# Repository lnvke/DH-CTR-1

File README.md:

DH/CTR-1. The successor to the DH/CTR-0. Now with more sensible design.

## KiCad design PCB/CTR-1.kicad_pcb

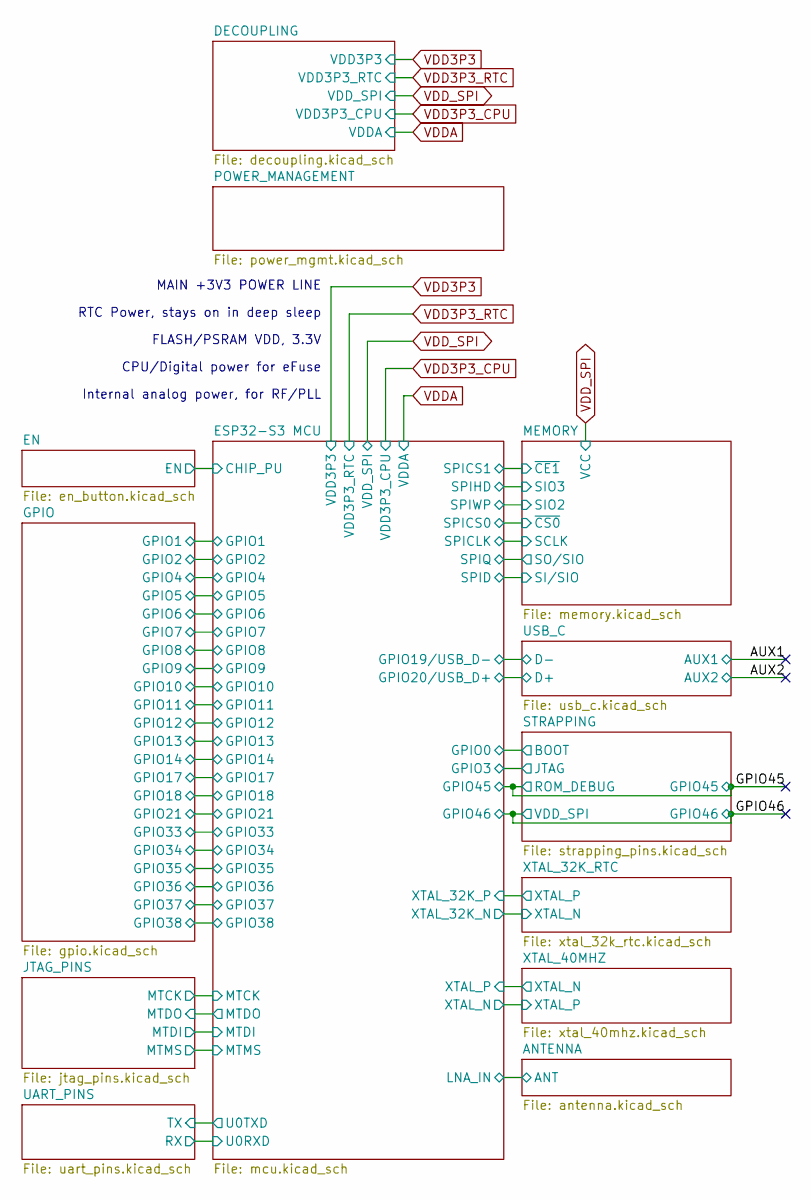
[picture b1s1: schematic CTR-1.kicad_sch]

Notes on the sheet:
Internal analog power, for RF/PLL
CPU/Digital power for eFuse
RTC Power, stays on in deep sleep
MAIN +3V3 POWER LINE
FLASH/PSRAM VDD, 3.3V

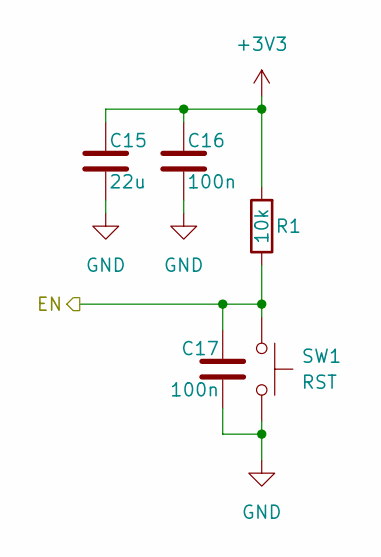
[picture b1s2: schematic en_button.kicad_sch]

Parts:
C15: 22u; C_0805_2012Metric
C16, C17: 100n; C_0603_1608Metric
R1: 10k; R_0603_1608Metric
SW1: RST; SW_Push_SPST_NO_Alps_SKRK

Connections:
+3V3: C15.1, C16.1, R1.2; also elsewhere on the board
/EN/EN: C17.1, R1.1, SW1.1; also elsewhere on the board
GND: C15.2, C16.2, C17.2, SW1.2; also elsewhere on the board

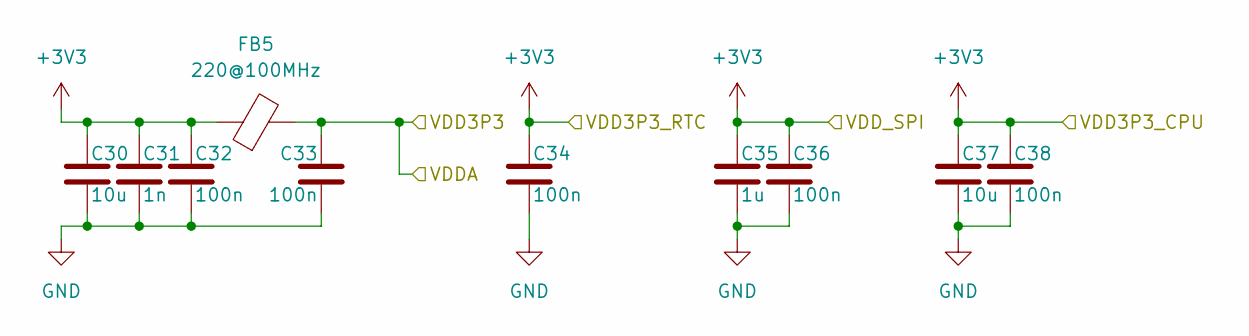
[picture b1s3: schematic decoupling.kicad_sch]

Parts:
C30: 10u; C_0805_2012Metric
C31: 1n; C_0402_1005Metric
C32: 100n; C_0402_1005Metric
C33, C34, C36, C38: 100n; C_0603_1608Metric
C35: 1u; C_0805_2012Metric
C37: 10u; C_0603_1608Metric
FB5: 220@100MHz; L_0805_2012Metric

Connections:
GND: C30.2, C31.2, C32.2, C33.2, C34.2, C35.2, C36.2, C37.2, C38.2; also elsewhere on the board
VDD3P3_RTC: C30.1, C31.1, C32.1, C34.1, C35.1, C36.1, C37.1, C38.1, FB5.1; also elsewhere on the board
VDDA: C33.1, FB5.2; also elsewhere on the board

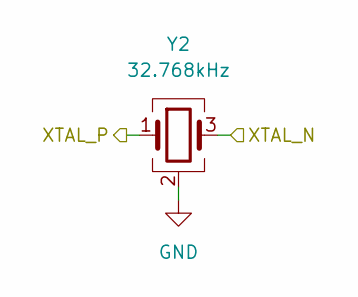
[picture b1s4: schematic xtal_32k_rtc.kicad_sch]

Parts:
Y2: 32.768kHz; Crystal_SMD_3225-4Pin_3.2x2.5mm

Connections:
/ESP32-S3 MCU/XTAL_32K_N: Y2.3; also elsewhere on the board
/ESP32-S3 MCU/XTAL_32K_P: Y2.1; also elsewhere on the board
GND: Y2.2 (G), Y2.4 (G); also elsewhere on the board

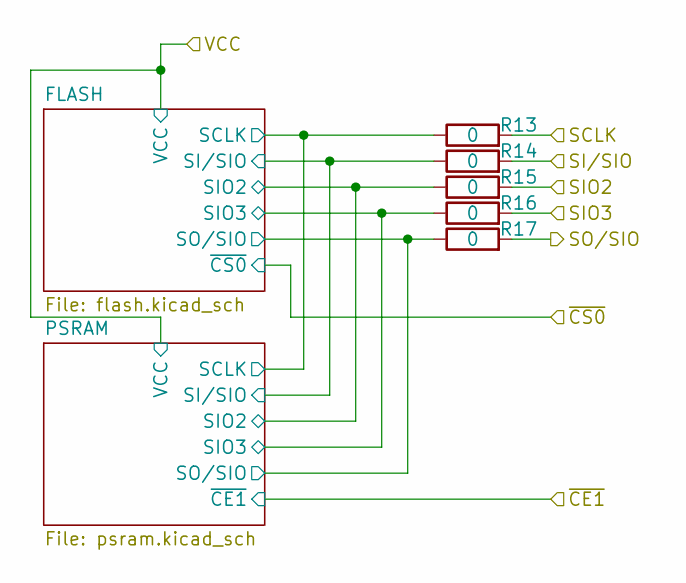
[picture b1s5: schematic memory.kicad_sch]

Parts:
R13, R14, R15, R16, R17: 0; R_0402_1005Metric

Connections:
/ESP32-S3 MCU/SPICLK: R13.2; also elsewhere on the board
/ESP32-S3 MCU/SPID: R14.2; also elsewhere on the board
/ESP32-S3 MCU/SPIHD: R16.2; also elsewhere on the board
/ESP32-S3 MCU/SPIQ: R17.2; also elsewhere on the board
/ESP32-S3 MCU/SPIWP: R15.2; also elsewhere on the board
/MEMORY/FLASH/SCLK: R13.1; also elsewhere on the board
/MEMORY/FLASH/SIO2: R15.1; also elsewhere on the board
/MEMORY/FLASH/SIO3: R16.1; also elsewhere on the board
/MEMORY/FLASH/SI/SIO: R14.1; also elsewhere on the board
/MEMORY/FLASH/SO/SIO: R17.1; also elsewhere on the board

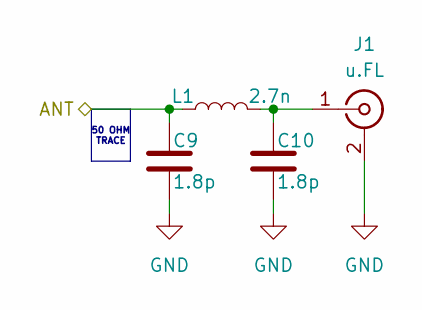
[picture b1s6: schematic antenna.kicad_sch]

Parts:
C9, C10: 1.8p; C_0603_1608Metric
J1: u.FL; U.FL_Hirose_U.FL-R-SMT-1_Vertical
L1: 2.7n; L_0402_1005Metric

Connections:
/ANTENNA/ANT: C9.1, L1.1; also elsewhere on the board
GND: C9.2, C10.2, J1.2 (Ext); also elsewhere on the board
unnamed: C10.1, J1.1 (In), L1.2

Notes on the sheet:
50 OHM TRACE

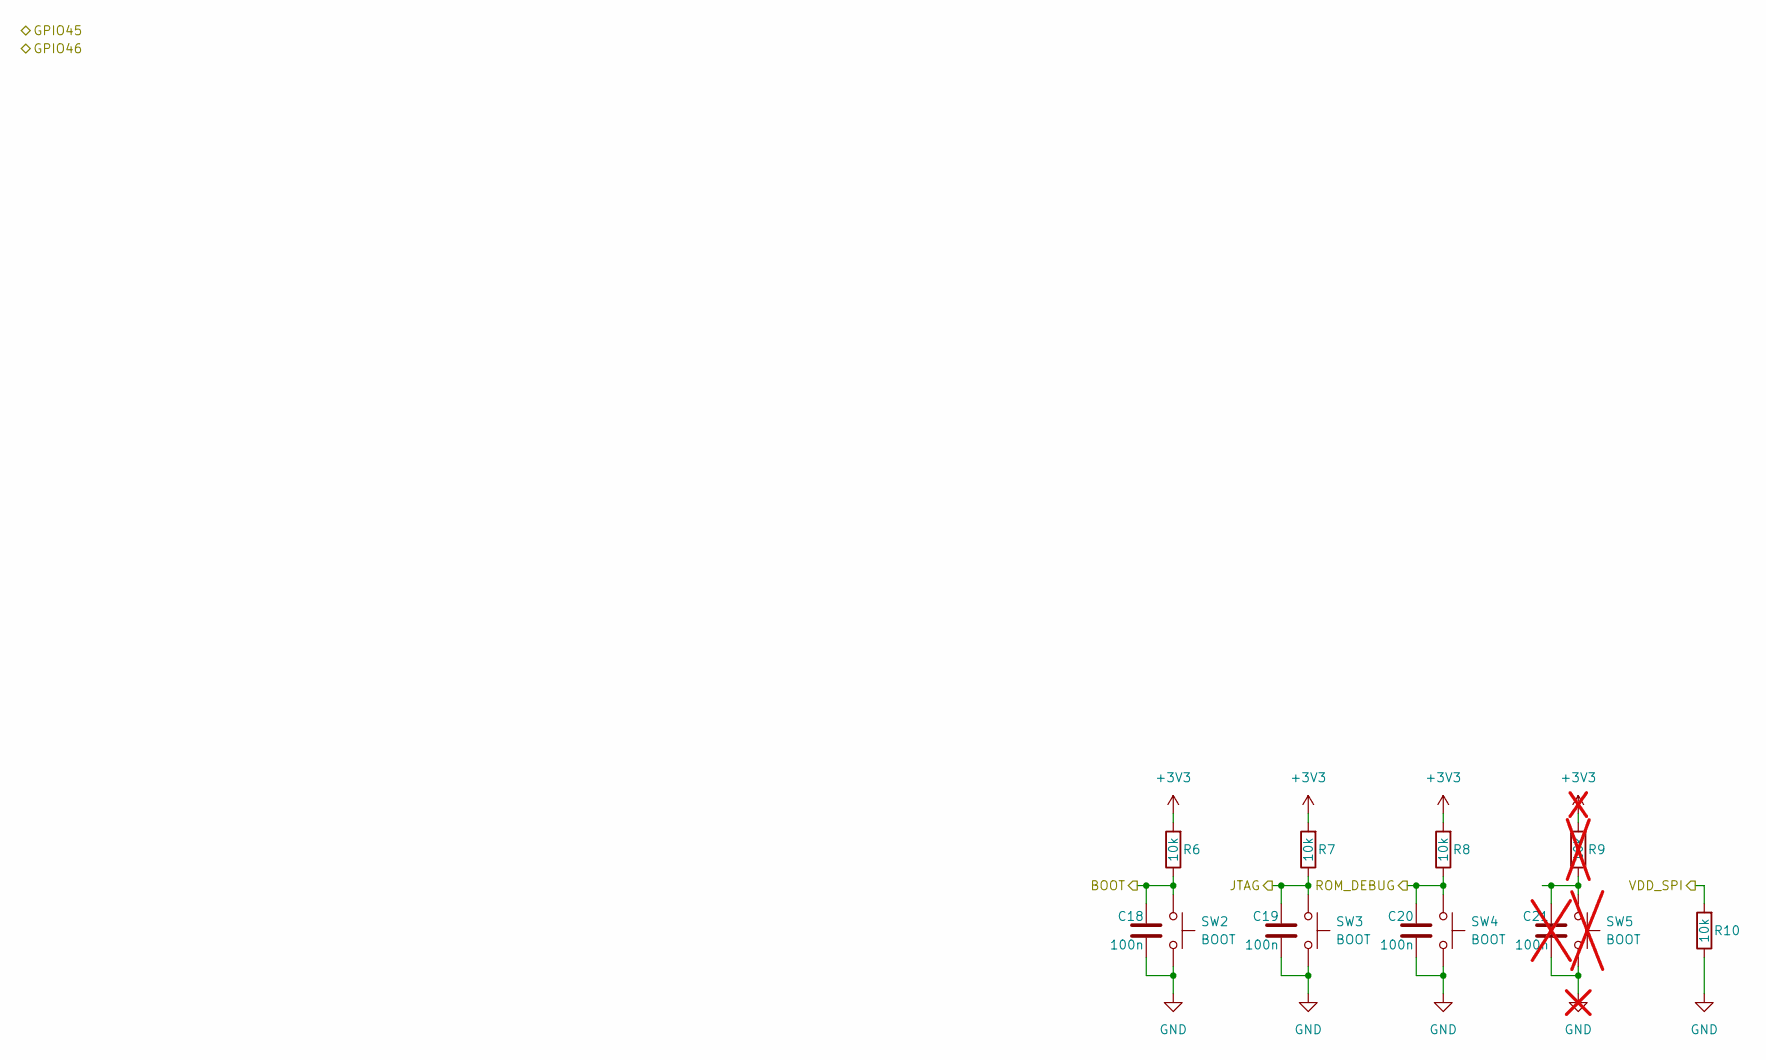
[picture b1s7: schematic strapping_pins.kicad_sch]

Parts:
C18, C19, C20: 100n; C_0603_1608Metric
C21: 100n; C_0603_1608Metric; not fitted
R6, R7, R8, R10: 10k; R_0603_1608Metric
R9: 10k; not fitted
SW2, SW3, SW4: BOOT; SW_Push_SPST_NO_Alps_SKRK
SW5: BOOT; SW_Push_SPST_NO_Alps_SKRK; not fitted

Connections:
+3V3: R6.2, R7.2, R8.2, R9.2; also elsewhere on the board
/ESP32-S3 MCU/GPIO0: C18.1, R6.1, SW2.1; also elsewhere on the board
/ESP32-S3 MCU/GPIO3: C19.1, R7.1, SW3.1; also elsewhere on the board
/GPIO45: C20.1, R8.1, SW4.1; also elsewhere on the board
/GPIO46: R10.2; also elsewhere on the board
GND: C18.2, C19.2, C20.2, C21.2, R10.1, SW2.2, SW3.2, SW4.2, SW5.2; also elsewhere on the board
unnamed: C21.1, R9.1, SW5.1

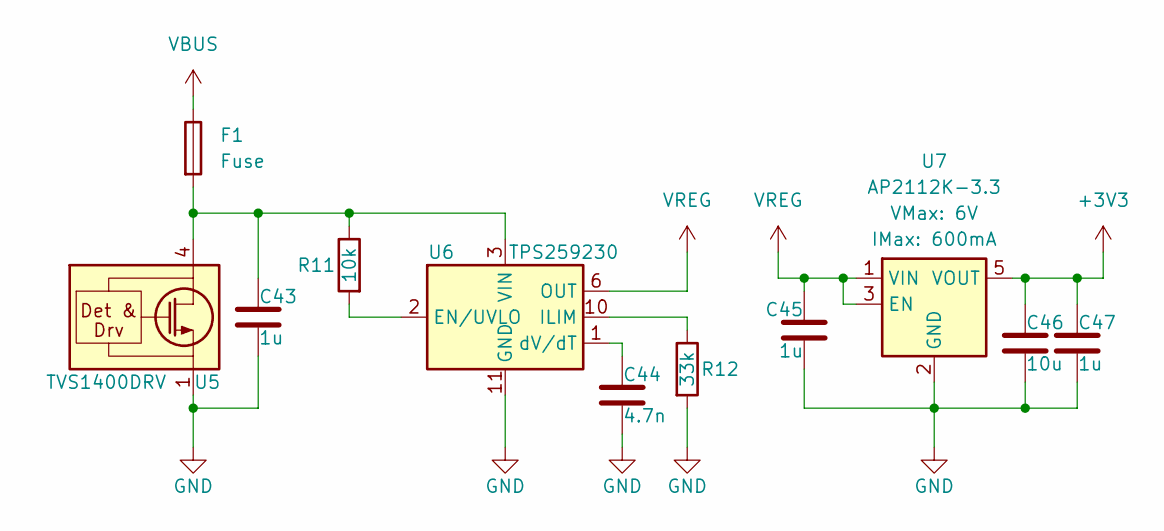
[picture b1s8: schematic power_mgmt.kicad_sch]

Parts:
C43, C45, C47: 1u; C_0805_2012Metric
C44: 4.7n; C_0603_1608Metric
C46: 10u; C_0805_2012Metric
F1: Fuse; Fuse_0603_1608Metric
R11: 10k; R_0603_1608Metric
R12: 33k; R_0603_1608Metric
U5: TVS1400DRV; WSON-6-1EP_2x2mm_P0.65mm_EP1x1.6mm
U6: TPS259230; VSON-10-1EP_3x3mm_P0.5mm_EP1.65x2.4mm_ThermalVias
U7: AP2112K-3.3; SOT-23-5

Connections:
+3V3: C46.1, C47.1, U7.5 (VOUT); also elsewhere on the board
GND: C43.2, C44.2, C45.2, C46.2, C47.2, R12.2, U5.1 (GND), U5.2 (GND), U5.3 (GND), U5.7 (GND), U6.11 (GND), U7.2 (GND); also elsewhere on the board
unnamed: C43.1, F1.2, R11.1, U5.4 (IN), U5.5 (IN), U5.6 (IN), U6.3 (VIN), U6.4 (VIN), U6.5 (VIN)
unnamed: R11.2, U6.2 (EN/UVLO)
unnamed: R12.1, U6.10 (ILIM)
unnamed: C44.1, U6.1 (dV/dT)
VBUS: F1.1; also elsewhere on the board
VREG: C45.1, U6.6 (OUT), U6.7 (OUT), U6.8 (OUT), U7.1 (VIN), U7.3 (EN); also elsewhere on the board

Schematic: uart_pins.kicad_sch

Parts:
J17: UART; PinHeader_1x04_P2.54mm_Vertical

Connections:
+3V3: J17.4; also elsewhere on the board
/ESP32-S3 MCU/U0RXD: J17.2; also elsewhere on the board
/ESP32-S3 MCU/U0TXD: J17.1; also elsewhere on the board
GND: J17.3; also elsewhere on the board

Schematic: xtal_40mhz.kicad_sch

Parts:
Y1: 40MHz; Crystal_SMD_3225-4Pin_3.2x2.5mm

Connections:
/ESP32-S3 MCU/XTAL_N: Y1.1; also elsewhere on the board
/ESP32-S3 MCU/XTAL_P: Y1.3; also elsewhere on the board
GND: Y1.2 (G), Y1.4 (G); also elsewhere on the board

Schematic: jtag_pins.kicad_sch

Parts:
J13: REF; PinHeader_1x02_P2.54mm_Vertical
J14: JTAG; PinHeader_1x04_P2.54mm_Vertical

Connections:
+3V3: J13.1; also elsewhere on the board
/ESP32-S3 MCU/MTCK: J14.1; also elsewhere on the board
/ESP32-S3 MCU/MTDI: J14.3; also elsewhere on the board
/ESP32-S3 MCU/MTDO: J14.2; also elsewhere on the board
/ESP32-S3 MCU/MTMS: J14.4; also elsewhere on the board
GND: J13.2; also elsewhere on the board

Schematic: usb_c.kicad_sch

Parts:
J2: USB_C_Receptacle_USB2.0_16P; USB_C_Receptacle_GCT_USB4105-xx-A_16P_TopMnt_Horizontal
R2, R3: 5.1k; R_0805_2012Metric
U2: USBLC6-2P6; SOT-666

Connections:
/AUX1: J2.A8 (SBU1)
/AUX2: J2.B8 (SBU2)
/ESP32-S3 MCU/GPIO19/USB_D-: U2.6 (I/O1); also elsewhere on the board
/ESP32-S3 MCU/GPIO20/USB_D+: U2.4 (I/O2); also elsewhere on the board
GND: J2.A1 (GND), J2.A12 (GND), J2.B1 (GND), J2.B12 (GND), J2.SH (SHIELD), R2.2, R3.2, U2.2 (GND); also elsewhere on the board
unnamed: J2.A5 (CC1), R2.1
unnamed: J2.B5 (CC2), R3.1
unnamed: J2.A6 (D+), J2.B6 (D+), U2.3 (I/O2)
unnamed: J2.A7 (D-), J2.B7 (D-), U2.1 (I/O1)
VBUS: J2.A4 (VBUS), J2.A9 (VBUS), J2.B4 (VBUS), J2.B9 (VBUS); also elsewhere on the board
VREG: U2.5 (VBUS); also elsewhere on the board

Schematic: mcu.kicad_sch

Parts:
U1: ESP32-S3; QFN-56-1EP_7x7mm_P0.4mm_EP4x4mm

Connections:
/ANTENNA/ANT: U1.1 (LNA_IN); also elsewhere on the board
/EN/EN: U1.4 (CHIP_PU); also elsewhere on the board
/ESP32-S3 MCU/GPIO0: U1.5 (GPIO0); also elsewhere on the board
/ESP32-S3 MCU/GPIO1: U1.6 (GPIO1); also elsewhere on the board
/ESP32-S3 MCU/GPIO2: U1.7 (GPIO2); also elsewhere on the board
/ESP32-S3 MCU/GPIO3: U1.8 (GPIO3); also elsewhere on the board
/ESP32-S3 MCU/GPIO4: U1.9 (GPIO4); also elsewhere on the board
/ESP32-S3 MCU/GPIO5: U1.10 (GPIO5); also elsewhere on the board
/ESP32-S3 MCU/GPIO6: U1.11 (GPIO6); also elsewhere on the board
/ESP32-S3 MCU/GPIO7: U1.12 (GPIO7); also elsewhere on the board
/ESP32-S3 MCU/GPIO8: U1.13 (GPIO8); also elsewhere on the board
/ESP32-S3 MCU/GPIO9: U1.14 (GPIO9); also elsewhere on the board
/ESP32-S3 MCU/GPIO10: U1.15 (GPIO10); also elsewhere on the board
/ESP32-S3 MCU/GPIO11: U1.16 (GPIO11); also elsewhere on the board
/ESP32-S3 MCU/GPIO12: U1.17 (GPIO12); also elsewhere on the board
/ESP32-S3 MCU/GPIO13: U1.18 (GPIO13); also elsewhere on the board
/ESP32-S3 MCU/GPIO14: U1.19 (GPIO14); also elsewhere on the board
/ESP32-S3 MCU/GPIO17: U1.23 (GPIO17); also elsewhere on the board
/ESP32-S3 MCU/GPIO18: U1.24 (GPIO18); also elsewhere on the board
/ESP32-S3 MCU/GPIO19/USB_D-: U1.25 (GPIO19/USB_D-); also elsewhere on the board
/ESP32-S3 MCU/GPIO20/USB_D+: U1.26 (GPIO20/USB_D+); also elsewhere on the board
/ESP32-S3 MCU/GPIO21: U1.27 (GPIO21); also elsewhere on the board
/ESP32-S3 MCU/GPIO33: U1.38 (GPIO33); also elsewhere on the board
/ESP32-S3 MCU/GPIO34: U1.39 (GPIO34); also elsewhere on the board
/ESP32-S3 MCU/GPIO35: U1.40 (GPIO35); also elsewhere on the board
/ESP32-S3 MCU/GPIO36: U1.41 (GPIO36); also elsewhere on the board
/ESP32-S3 MCU/GPIO37: U1.42 (GPIO37); also elsewhere on the board
/ESP32-S3 MCU/GPIO38: U1.43 (GPIO38); also elsewhere on the board
/ESP32-S3 MCU/MTCK: U1.44 (MTCK); also elsewhere on the board
/ESP32-S3 MCU/MTDI: U1.47 (MTDI); also elsewhere on the board
/ESP32-S3 MCU/MTDO: U1.45 (MTDO); also elsewhere on the board
/ESP32-S3 MCU/MTMS: U1.48 (MTMS); also elsewhere on the board
/ESP32-S3 MCU/SPICLK: U1.33 (SPICLK); also elsewhere on the board
/ESP32-S3 MCU/SPICS0: U1.32 (SPICS0); also elsewhere on the board
/ESP32-S3 MCU/SPICS1: U1.28 (SPICS1); also elsewhere on the board
/ESP32-S3 MCU/SPID: U1.35 (SPID); also elsewhere on the board
/ESP32-S3 MCU/SPIHD: U1.30 (SPIHD); also elsewhere on the board
/ESP32-S3 MCU/SPIQ: U1.34 (SPIQ); also elsewhere on the board
/ESP32-S3 MCU/SPIWP: U1.31 (SPIWP); also elsewhere on the board
/ESP32-S3 MCU/U0RXD: U1.50 (U0RXD); also elsewhere on the board
/ESP32-S3 MCU/U0TXD: U1.49 (U0TXD); also elsewhere on the board
/ESP32-S3 MCU/XTAL_32K_N: U1.22 (XTAL_32K_N); also elsewhere on the board
/ESP32-S3 MCU/XTAL_32K_P: U1.21 (XTAL_32K_P); also elsewhere on the board
/ESP32-S3 MCU/XTAL_N: U1.53 (XTAL_N); also elsewhere on the board
/ESP32-S3 MCU/XTAL_P: U1.54 (XTAL_P); also elsewhere on the board
/GPIO45: U1.51 (GPIO45); also elsewhere on the board
/GPIO46: U1.52 (GPIO46); also elsewhere on the board
GND: U1.57 (GND); also elsewhere on the board
VDD3P3_RTC: U1.20 (VDD3P3_RTC), U1.29 (VDD_SPI), U1.46 (VDD3P3_CPU); also elsewhere on the board
VDDA: U1.2 (VDD3P3), U1.3 (VDD3P3), U1.55 (VDDA), U1.56 (VDDA); also elsewhere on the board

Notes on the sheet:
CLK
HPST
(GPIO41)
(GPIO15)
SPI_MEM
RTC
USB
(GPIO39)
(GPIO16)
(GPIO43)
(GPIO44)
JTAG
(GPIO40)
UART
(GPIO42)
BUTTON
NOT FOR QSPI

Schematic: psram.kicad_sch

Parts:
U3: ESP-PSRAM64H; SOIC-8_3.9x4.9mm_P1.27mm

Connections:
/ESP32-S3 MCU/SPICS1: U3.1 (~CE); also elsewhere on the board
/MEMORY/FLASH/SCLK: U3.6 (SCLK); also elsewhere on the board
/MEMORY/FLASH/SIO2: U3.3 (SIO2); also elsewhere on the board
/MEMORY/FLASH/SIO3: U3.7 (SIO3); also elsewhere on the board
/MEMORY/FLASH/SI/SIO: U3.5 (SI/SIO); also elsewhere on the board
/MEMORY/FLASH/SO/SIO: U3.2 (SO/SIO); also elsewhere on the board
GND: U3.4 (VSS); also elsewhere on the board
VDD3P3_RTC: U3.8 (VCC); also elsewhere on the board

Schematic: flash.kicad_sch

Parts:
U4: W25Q128JVS; SOIC-8_5.3x5.3mm_P1.27mm

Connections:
/ESP32-S3 MCU/SPICS0: U4.1 (~CS); also elsewhere on the board
/MEMORY/FLASH/SCLK: U4.6 (CLK); also elsewhere on the board
/MEMORY/FLASH/SIO2: U4.3 (~WP/IO_{2}); also elsewhere on the board
/MEMORY/FLASH/SIO3: U4.7 (~HOLD/~RESET/IO_{3}); also elsewhere on the board
/MEMORY/FLASH/SI/SIO: U4.5 (DI/IO_{0}); also elsewhere on the board
/MEMORY/FLASH/SO/SIO: U4.2 (DO/IO_{1}); also elsewhere on the board
GND: U4.4 (GND); also elsewhere on the board
VDD3P3_RTC: U4.8 (VCC); also elsewhere on the board

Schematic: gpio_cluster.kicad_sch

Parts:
C22: 100n; C_0603_1608Metric
C23: 10u; C_0805_2012Metric
FB1: 220@100MHz; L_0805_2012Metric
J3: GPIO; PinHeader_1x04_P2.54mm_Vertical
J4: REF; PinHeader_1x02_P2.54mm_Vertical

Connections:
/ESP32-S3 MCU/GPIO1: J3.1; also elsewhere on the board
/ESP32-S3 MCU/GPIO2: J3.2; also elsewhere on the board
/ESP32-S3 MCU/GPIO4: J3.3; also elsewhere on the board
/ESP32-S3 MCU/GPIO5: J3.4; also elsewhere on the board
/GPIO/GPIO_CLUSTER/cVDD: FB1.2
GND: C22.1, C23.1, J4.2; also elsewhere on the board
unnamed: C22.2, C23.2, FB1.1, J4.1

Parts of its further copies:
C24, C26, C28, C39, C41: 100n; C_0603_1608Metric
C25, C27, C29, C40, C42: 10u; C_0805_2012Metric
FB2, FB3, FB4, FB6, FB7: 220@100MHz; L_0805_2012Metric
J5, J7, J9, J11, J15: GPIO; PinHeader_1x04_P2.54mm_Vertical
J6, J8, J10, J12, J16: REF; PinHeader_1x02_P2.54mm_Vertical

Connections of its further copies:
+3V3: FB2.2, FB3.2, FB4.2, FB6.2, FB7.2; also elsewhere on the board
/ESP32-S3 MCU/GPIO6: J5.1; also elsewhere on the board
/ESP32-S3 MCU/GPIO7: J5.2; also elsewhere on the board
/ESP32-S3 MCU/GPIO8: J5.3; also elsewhere on the board
/ESP32-S3 MCU/GPIO9: J5.4; also elsewhere on the board
/ESP32-S3 MCU/GPIO10: J7.1; also elsewhere on the board
/ESP32-S3 MCU/GPIO11: J7.2; also elsewhere on the board
/ESP32-S3 MCU/GPIO12: J7.3; also elsewhere on the board
/ESP32-S3 MCU/GPIO13: J7.4; also elsewhere on the board
/ESP32-S3 MCU/GPIO14: J9.1; also elsewhere on the board
/ESP32-S3 MCU/GPIO17: J9.2; also elsewhere on the board
/ESP32-S3 MCU/GPIO18: J9.3; also elsewhere on the board
/ESP32-S3 MCU/GPIO21: J9.4; also elsewhere on the board
/ESP32-S3 MCU/GPIO33: J11.1; also elsewhere on the board
/ESP32-S3 MCU/GPIO34: J11.2; also elsewhere on the board
/ESP32-S3 MCU/GPIO35: J11.3; also elsewhere on the board
/ESP32-S3 MCU/GPIO36: J11.4; also elsewhere on the board
/ESP32-S3 MCU/GPIO37: J15.1; also elsewhere on the board
/ESP32-S3 MCU/GPIO38: J15.2; also elsewhere on the board
/GPIO/GPIO_CLUSTER5/cGPIO3: J15.3
/GPIO/GPIO_CLUSTER5/cGPIO4: J15.4
GND: C24.1, C25.1, C26.1, C27.1, C28.1, C29.1, C39.1, C40.1, C41.1, C42.1, J6.2, J8.2, J10.2, J12.2, J16.2; also elsewhere on the board
unnamed: C24.2, C25.2, FB2.1, J6.1
unnamed: C26.2, C27.2, FB3.1, J8.1
unnamed: C28.2, C29.2, FB4.1, J10.1
unnamed: C39.2, C40.2, FB6.1, J12.1
unnamed: C41.2, C42.2, FB7.1, J16.1

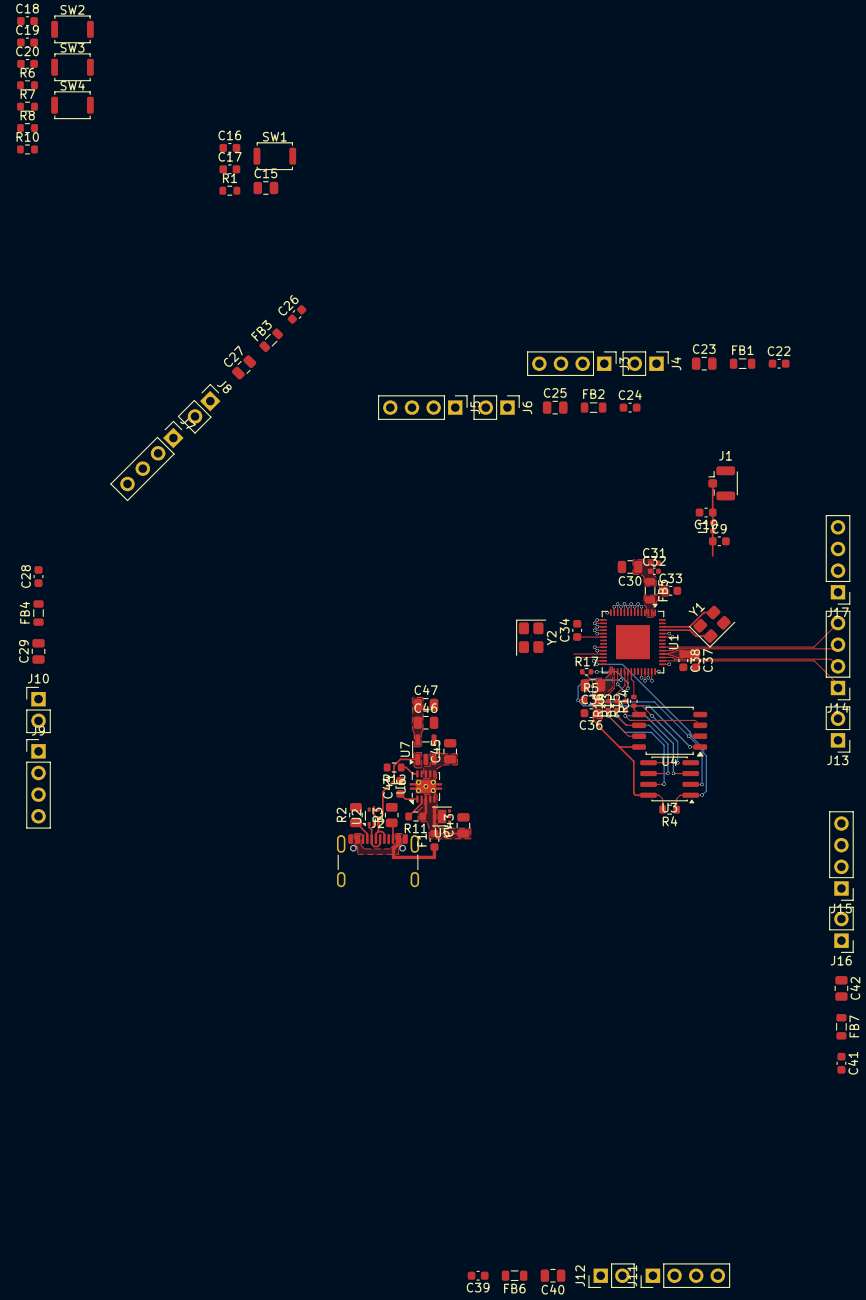
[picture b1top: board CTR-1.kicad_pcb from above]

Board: 4 copper layers, 89 parts (0 on the bottom side), 73 nets.

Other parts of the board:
R4, R5: 10k; R_0603_1608Metric

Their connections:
/ESP32-S3 MCU/SPICS0: R5.1; also elsewhere on the board
/ESP32-S3 MCU/SPICS1: R4.1; also elsewhere on the board
VDD3P3_RTC: R4.2, R5.2; also elsewhere on the board
